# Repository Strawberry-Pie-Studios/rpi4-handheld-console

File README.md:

🚧 Work in Progress (50% Complete): Schematic and initial PCB routing are underway—do not manufacture yet!

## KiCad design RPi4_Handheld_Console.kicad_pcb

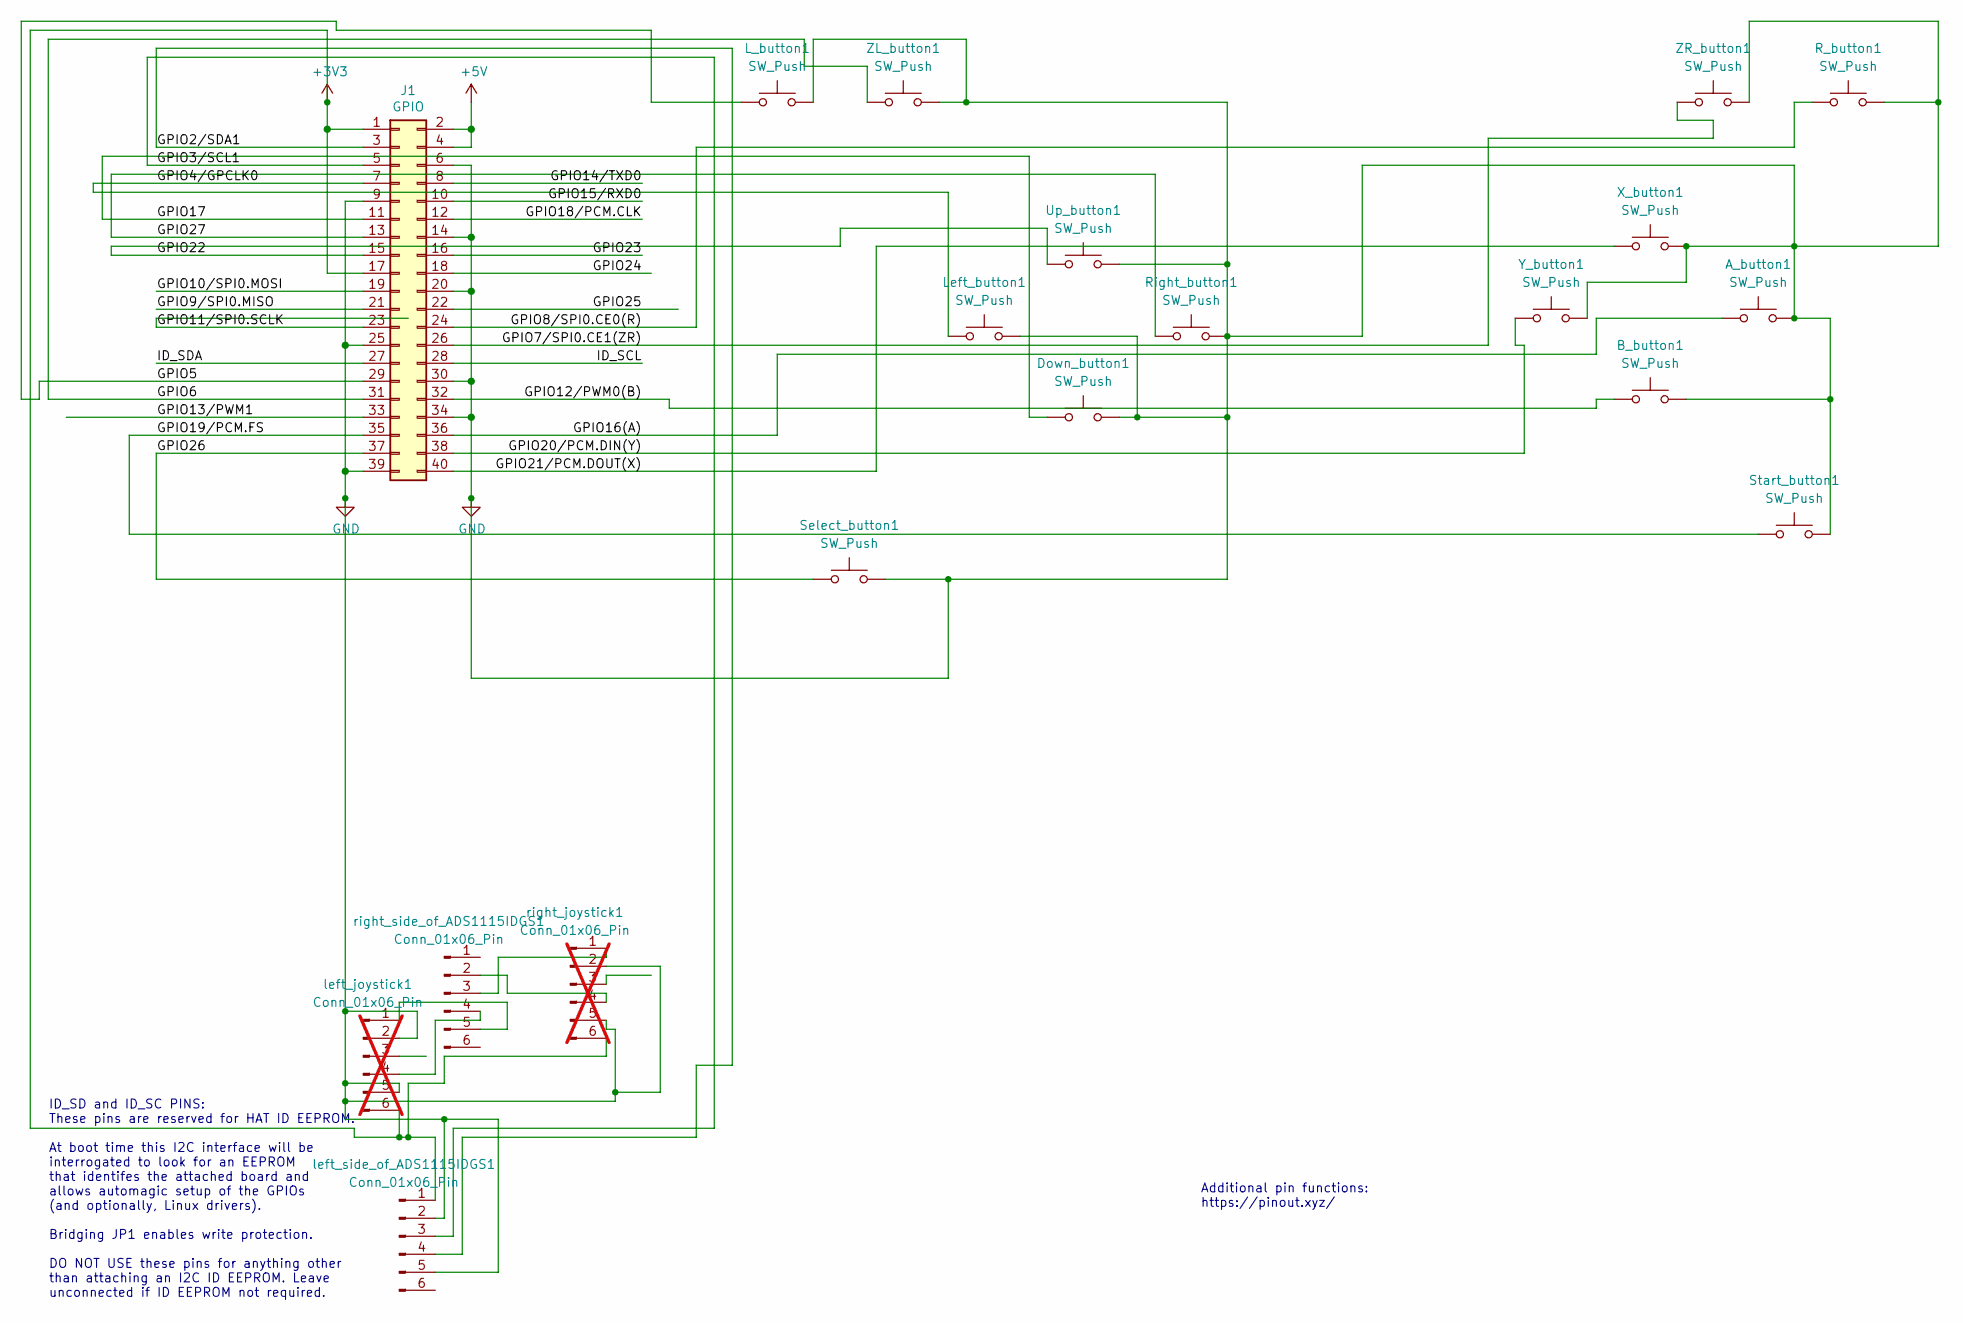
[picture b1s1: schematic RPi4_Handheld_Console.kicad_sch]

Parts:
A_button1: SW_Push; SW_PUSH_6mm_H4.3mm
B_button1: SW_Push; SW_PUSH_6mm_H4.3mm
Down_button1: SW_Push; SW_PUSH_6mm_H4.3mm
J1: GPIO; PinHeader_2x20_P2.54mm_Vertical
L_button1: SW_Push; SW_Tactile_SKHH_Angled
Left_button1: SW_Push; SW_PUSH_6mm_H4.3mm
R_button1: SW_Push; SW_Tactile_SKHH_Angled
Right_button1: SW_Push; SW_PUSH_6mm_H4.3mm
Select_button1: SW_Push; SW_PUSH_6mm_H4.3mm
Start_button1: SW_Push; SW_PUSH_6mm_H4.3mm
Up_button1: SW_Push; SW_PUSH_6mm_H4.3mm
X_button1: SW_Push; SW_PUSH_6mm_H4.3mm
Y_button1: SW_Push; SW_PUSH_6mm_H4.3mm
ZL_button1: SW_Push; SW_Tactile_SKHH_Angled
ZR_button1: SW_Push; SW_Tactile_SKHH_Angled
left_joystick1: Conn_01x06_Pin; PinHeader_1x06_P2.00mm_Vertical; not fitted
left_side_of_ADS1115IDGS1: Conn_01x06_Pin; PinHeader_1x06_P2.54mm_Vertical
right_joystick1: Conn_01x06_Pin; PinHeader_1x06_P2.00mm_Vertical; not fitted
right_side_of_ADS1115IDGS1: Conn_01x06_Pin; PinHeader_1x06_P2.54mm_Vertical

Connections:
+3V3: J1.1, J1.17, left_joystick1.6, left_side_of_ADS1115IDGS1.1, right_joystick1.6
+5V: J1.2, J1.4
/GPIO2/SDA1: J1.3, left_side_of_ADS1115IDGS1.4
/GPIO3/SCL1: J1.5, left_side_of_ADS1115IDGS1.3
/GPIO4/GPCLK0: J1.7, Left_button1.1
/GPIO5: J1.29, L_button1.1
/GPIO6: J1.31, ZL_button1.1
/GPIO7/SPI0.CE1(ZR): J1.26, ZR_button1.1
/GPIO8/SPI0.CE0(R): J1.24, R_button1.1
/GPIO9/SPI0.MISO: J1.21
/GPIO10/SPI0.MOSI: J1.19
/GPIO11/SPI0.SCLK: J1.23
/GPIO12/PWM0(B): B_button1.1, J1.32
/GPIO13/PWM1: J1.33
/GPIO14/TXD0: J1.8
/GPIO15/RXD0: J1.10
/GPIO16(A): A_button1.1, J1.36
/GPIO17: Down_button1.1, J1.11
/GPIO18/PCM.CLK: J1.12
/GPIO19/PCM.FS: J1.35, Start_button1.1
/GPIO20/PCM.DIN(Y): J1.38, Y_button1.1
/GPIO21/PCM.DOUT(X): J1.40, X_button1.1
/GPIO22: J1.15, Up_button1.1
/GPIO23: J1.16
/GPIO24: J1.18
/GPIO25: J1.22
/GPIO26: J1.37, Select_button1.1
/GPIO27: J1.13, Right_button1.1
/ID_SCL: J1.28
/ID_SDA: J1.27
GND: A_button1.2, B_button1.2, Down_button1.2, J1.6, J1.9, J1.14, J1.20, J1.25, J1.30, J1.34, J1.39, L_button1.2, Left_button1.2, R_button1.2, Right_button1.2, Select_button1.2, Start_button1.2, Up_button1.2, X_button1.2, Y_button1.2, ZL_button1.2, ZR_button1.2, left_joystick1.2, left_joystick1.5, left_side_of_ADS1115IDGS1.2, left_side_of_ADS1115IDGS1.5, right_joystick1.2, right_joystick1.5
unnamed: left_joystick1.1, right_side_of_ADS1115IDGS1.5
unnamed: left_joystick1.4, right_side_of_ADS1115IDGS1.4
unnamed: right_joystick1.1, right_side_of_ADS1115IDGS1.3
unnamed: right_joystick1.4, right_side_of_ADS1115IDGS1.2

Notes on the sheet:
Additional pin functions: https://pinout.xyz/
ID_SD and ID_SC PINS: These pins are reserved for HAT ID EEPROM. At boot time this I2C interface will be interrogated to look for an EEPROM that identifes the attached board and allows automagic setup of the GPIOs (and optionally, Linux drivers). Bridging JP1 enables write protection. DO NOT USE th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

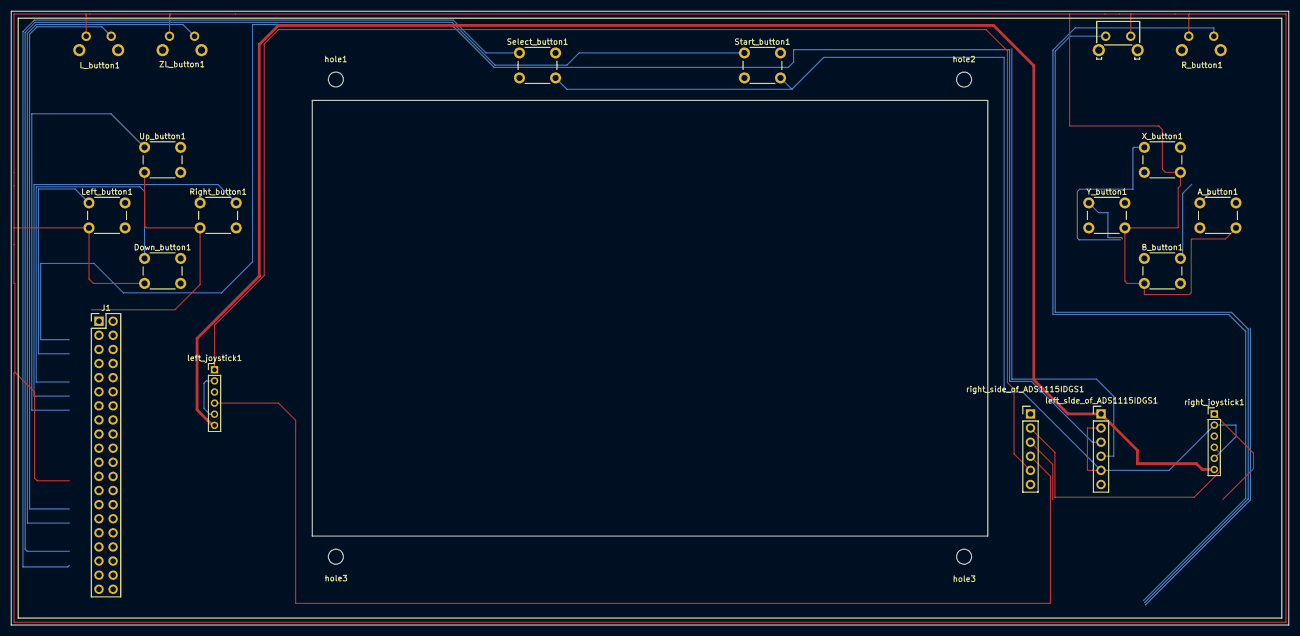
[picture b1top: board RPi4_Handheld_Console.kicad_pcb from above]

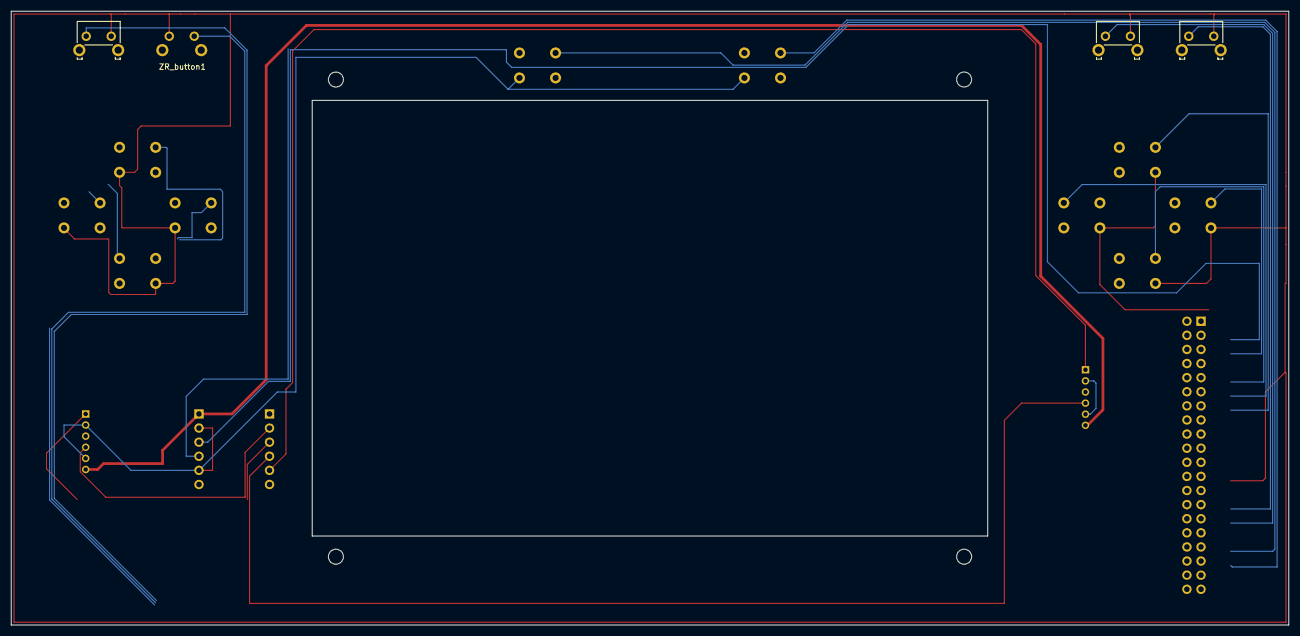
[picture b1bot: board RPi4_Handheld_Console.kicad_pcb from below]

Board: 2 copper layers, 230.0 x 110.5 mm, 23 parts (3 on the bottom side), 23 nets.

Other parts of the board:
hole1, hole2, hole3, hole3#2: MountingHole_2.7mm_M2.5
